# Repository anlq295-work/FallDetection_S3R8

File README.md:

# FallDetection_S3R8 (Fall Guard S3R8)

Hệ thống giám sát và phát hiện té ngã không tiếp xúc (non-contact, bảo vệ quyền riêng tư không dùng camera) chạy trên **ESP32-S3 N16R8** (16MB Flash, 8MB Octal PSRAM), kết hợp cảm biến đa phương thức (**ToF VL53L1X + 24GHz FMCW Radar HLK-LD2410B + PIR AM312**), bộ suy luận **Edge AI lai đa tiêu chí** và ứng dụng di động đa nền tảng **Flutter (Android & iOS)**.

> **Phiên bản hiện tại:** Firmware `Pre-release2.0.1` · Mobile App **Hearth** `Pre-release2.0.1` (`2.0.1+1`) · Target MCU: `esp32-s3-devkitc-1` (`qio_opi`)

---

## Mục lục

- [Tổng quan kiến trúc](#tổng-quan-kiến-trúc)
- [Tính năng nổi bật](#tính-năng-nổi-bật)
- [Cấu trúc thư mục](#cấu-trúc-thư-mục)
- [Phần cứng & Sơ đồ nối chân](#phần-cứng--sơ-đồ-nối-chân)
- [Thuật toán Edge AI & Máy trạng thái (FSM)](#thuật-toán-edge-ai--máy-trạng-thái-fsm)
- [Hướng dẫn Build & Cài đặt](#hướng-dẫn-build--cài-đặt)
- [Giao tiếp BLE, REST API & Lệnh điều khiển](#giao-tiếp-ble-rest-api--lệnh-điều-khiển)
- [Cập nhật Firmware OTA](#cập-nhật-firmware-ota)
- [CI/CD & Tự động phát hành](#cicd--tự-động-phát-hành)
- [Xử lý sự cố thường gặp](#xử-lý-sự-cố-thường-gặp)

---

## Tổng quan kiến trúc

```mermaid
flowchart LR
    subgraph SENSORS["Cụm cảm biến (20 Hz)"]
        TOF["VL53L1X ToF<br/>(I2C GPIO8/9)"]
        RADAR["HLK-LD2410B 24GHz Radar<br/>(UART2 GPIO17/18)"]
        PIR["PIR AM312<br/>(GPIO4 RTC IRQ)"]
        TOUCH["Touch SOS / Cancel<br/>(GPIO7)"]
    end

    subgraph MCU["ESP32-S3 N16R8 (16MB Flash / 8MB PSRAM)"]
        BUF["Circular Buffer (40 mẫu / 2s)<br/>Octal PSRAM"]
        AI["Edge AI Hybrid Engine<br/>(MLP 7→16→8→4 + Kinematic + Spatial)"]
        FSM["FSM 7 trạng thái<br/>+ WDT 10s + Hộp đen NVS"]
        LOCAL["WS2812B (24 LED) + Buzzer<br/>+ Smart Nightlight"]
        COMM["BLE GATT Server<br/>+ Wi-Fi Web Server (Port 80)<br/>+ OTA Manager"]
    end

    subgraph EXTERNAL["Giám sát & Cảnh báo từ xa"]
        APP["Flutter Mobile App<br/>(Android / iOS)"]
        TG["Telegram Bot API<br/>(HTML Alert)"]
        SMS["SpeedSMS Gateway"]
        GH["GitHub Releases<br/>(firmware.bin / APK / IPA)"]
    end

    TOF & RADAR & PIR --> BUF --> AI --> FSM
    TOUCH --> FSM
    FSM --> LOCAL
    FSM --> COMM
    COMM <-->|BLE / Wi-Fi LAN| APP
    COMM -->|HTTPS + Auto Retry| TG & SMS
    GH -->|HTTP / BLE / Web OTA| COMM
```

---

## Tính năng nổi bật

### 1. Firmware ESP32-S3 (`src/`)
- **Cảm biến đa phương thức & tự phục hồi lỗi:**
  - **VL53L1X (ToF):** Đo khoảng cách/chiều cao cơ thể qua I2C `100 kHz` (địa chỉ `0x29`, chế độ `Medium`, timing budget `40 ms`), tự giải phóng bus I2C bằng 9 xung clock nếu đường SDA bị treo `LOW` và tự khởi tạo lại khi mất dữ liệu.
  - **HLK-LD2410B (Radar mmWave 24GHz):** Tự động dò tốc độ baud (`256000` ↔ `115200`), bật **Engineering Mode** thu 9 cổng năng lượng chuyển động (va chạm) và 9 cổng năng lượng tĩnh (hô hấp/hiện diện).
  - **PIR AM312:** Phát hiện chuyển động hồng ngoại qua ngắt ngoài GPIO4 (có thể bật/tắt bằng macro `ENABLE_PIR_SENSOR`).
  - **Bộ đệm trượt Octal PSRAM:** Lấy mẫu `20 Hz` (chu kỳ `50 ms`), lưu cửa sổ trượt `40` mẫu (`2.0 s`) trực tiếp trên PSRAM ngoài (`MALLOC_CAP_SPIRAM`).
- **Phát hiện 3 kịch bản khẩn cấp:**
  1. **Té ngã va chạm mạnh (`EVENT_FALL_IMPACT`):** Kết hợp tốc độ sụt giảm chiều cao ToF, đỉnh động năng Radar và khoảng cách sát sàn, sau đó xác minh bất động `2 s` kèm tín hiệu tĩnh hô hấp.
  2. **Ngã chậm / Ngất lịm (`EVENT_SLOW_FALL`):** Nằm sát sàn (`<= floorThresholdMm`), ít chuyển động nhưng còn tín hiệu hiện diện/hô hấp kéo dài quá `15 s`.
  3. **SOS thủ công (`EVENT_MANUAL_SOS`):** Chạm giữ cảm biến touch (GPIO7) trong `3 s` hoặc kích hoạt lệnh `PANIC_SOS` từ xa.
- **Giảm báo động giả & tự giải trừ:**
  - Lọc phân biệt hành động ngồi xuống ghế (*SIT Rejection*).
  - Cảnh báo tại chỗ tầng 1 (`PRE_ALARM`) kéo dài `30 s` cho phép người dùng chạm nút hủy hoặc **tự đứng dậy vững vàng trong `1.5 s`** để hệ thống tự hủy cảnh báo.
- **Hoạt động độc lập khi không có điện thoại ở gần:**
  - Tự gửi cảnh báo trực tiếp qua **Telegram Bot API** (hỗ trợ nhiều Chat ID/Group ID phân tách bằng `,` hoặc `;`) và **SMS Gateway (SpeedSMS)** (hỗ trợ nhiều số điện thoại).
  - Nếu Wi-Fi bị gián đoạn đúng lúc có sự cố, firmware tự giữ hàng đợi và gửi lại định kỳ (`10 s` khi chờ Wi-Fi, `30 s` khi lỗi HTTP) cho tới khi thành công.
- **Tiện ích bổ trợ & An toàn hệ thống:**
  - **Đèn ngủ thông minh (Smart Nightlight):** Tự bật ánh sáng vàng ấm `40 s` trên dải LED WS2812B khi phát hiện di chuyển trong khung giờ hẹn lịch (mặc định `18:00 – 06:00`, đồng bộ giờ qua NTP `UTC+7`).
  - **Còi báo động chống tự kêu lúc boot:** Ngắt phần cứng ngay microgiây đầu tiên (`earlyHardwareMute()`), hỗ trợ đổi phân cực **Active-LOW / Active-HIGH** và **Mute/Unmute** lưu bền vững trong NVS Flash.
  - **Hộp đen NVS Flash:** Lưu vòng tròn 5 sự kiện té ngã gần nhất (loại sự kiện, uptime, tốc độ rơi, đỉnh động năng, cự ly radar).
  - **Hardware Watchdog Timer (`10 s`):** Tự reset nếu hệ thống treo.

### 2. Ứng dụng di động Flutter (`mobile_app/`)
- **Đa nền tảng Android & iOS**, giao diện Material 3 hỗ trợ chế độ Sáng/Tối theo hệ thống.
- **Kết nối kép BLE & Wi-Fi Direct LAN:** Quét thiết bị `FallDetector_S3R8`, cấu hình Wi-Fi, danh bạ cứu hộ (SĐT, Telegram Bot Token, Chat ID), ngưỡng sàn `floor_mm`, lịch đèn ngủ và phân cực/tắt tiếng còi.
- **Giám sát thời gian thực:** Hiển thị trạng thái FSM, phân loại tư thế AI + độ tin cậy, biểu đồ telemetry (`LiveTelemetryChart`), mô phỏng tư thế người (`HumanPostureSimulation`), và Hộp đen lịch sử sự cố.
- **Bộ công cụ chăm sóc & y tế cho người cao tuổi:**
  - Hướng dẫn sơ cứu trực quan từng bước (`FirstAidGuideDialog`).
  - Hồ sơ y tế khẩn cấp & Thẻ Medical ID (`ElderlyMedicalProfile`, `EmergencyMedicalIdCardDialog`).
  - Đánh giá nguy cơ té ngã theo chuẩn **CDC STEADI** (`CdcSteadiAssessmentDialog`).
  - Xuất/xem Báo cáo kiểm tra y tế (`MedicalAuditReportDialog`) & hộp thoại báo động khẩn cấp toàn màn hình (`CriticalEmergencyAlarmDialog`).
- **Cập nhật In-App OTA:** Tự kiểm tra bản phát hành mới nhất từ GitHub Releases cho cả ứng dụng lẫn firmware ESP32.

---

## Cấu trúc thư mục

```text
FallDetection_S3R8/
├── platformio.ini                 # Cấu hình PlatformIO cho ESP32-S3 N16R8 (16MB Flash, OPI PSRAM)
├── HARDWARE_PINOUT.md             # Chi tiết sơ đồ đấu nối & lưu ý cấp nguồn 5V
├── src/
│   ├── config.h                   # Pinout, ngưỡng động học, hằng số thời gian, enum FSM/AI
│   ├── main.cpp                   # Setup/Loop, FSM 7 trạng thái, xử lý lệnh BLE/HTTP/Serial & retry SOS
│   ├── sensors.h / sensors.cpp    # Driver VL53L1X, parser LD2410B auto-baud, PIR ISR, circular buffer PSRAM
│   ├── edge_ai.h / edge_ai.cpp    # Mạng MLP (7-16-8-4) + chấm điểm động học/không gian (Hybrid Fusion)
│   ├── model_data.h               # Dữ liệu tham chiếu mô hình INT8 (TFLM)
│   ├── alert_system.h / .cpp      # Điều khiển WS2812B, Buzzer patterns, Nightlight, Wi-Fi, Telegram & SMS
│   ├── ble_provision.h / .cpp     # BLE GATT Server (6 characteristics), NVS config & Hộp đen 5 sự kiện
│   ├── web_server.h / .cpp        # HTTP Server cổng 80 (REST API + trang Web OTA /update)
│   └── ota_manager.h / .cpp       # Quản lý HTTP/HTTPS OTA và BLE OTA chunk stream
├── alert_bot/                     # Bot cảnh báo đa kênh (Telegram tương tác + SMS + CallMeBot/Twilio Voice)
│   ├── server.py                  # FastAPI REST API + Webhook nhận sự kiện ngã (/api/alerts/fall)
│   ├── dispatcher.py              # Phát cảnh báo đồng thời / leo thang tuần tự + xác nhận/đóng sự cố
│   ├── telegram_poller.py         # Telegram Bot (/start, /register, /settings, /contacts, /test, nút bấm)
│   ├── providers/                 # Telegram Bot API, SpeedSMS VN, Twilio SMS/Voice, CallMeBot Telegram Call
│   └── tests/                     # Unit & integration tests (pytest)
├── mobile_app/                    # Ứng dụng Flutter (Android & iOS)
│   ├── pubspec.yaml               # Dependencies: flutter_blue_plus, url_launcher, shared_preferences, ...
│   ├── README.md                  # Tài liệu riêng cho ứng dụng di động
│   └── lib/
│       ├── main.dart              # Entrypoint, Theme Material 3 & khai báo BLE UUID
│       ├── startup.dart           # Cổng xin quyền Bluetooth/Nearby Devices khi khởi động
│       ├── dashboard.dart         # Màn hình quét, kết nối & tổng quan thiết bị
│       ├── device_detail.dart     # Bảng điều khiển chi tiết, cấu hình thiết bị, OTA & Hộp đen
│       ├── telemetry_widgets.dart # Biểu đồ telemetry & mô phỏng tư thế người
│       ├── settings.dart          # Cài đặt chung, đơn vị đo & kiểm tra cập nhật GitHub Release
│       └── dialogs.dart           # Sơ cứu, Hồ sơ y tế, CDC STEADI, báo cáo y tế & cảnh báo SOS
├── ios_ota/
│   └── manifest.plist             # Manifest cài đặt OTA cho iOS
├── scripts/
│   └── pull_artifacts.py          # Script Python tải tự động APK/IPA/Firmware từ GitHub Actions
└── .github/workflows/
    └── build_apps.yml             # CI/CD build Android APK, iOS IPA, ESP32 firmware & publish Release
```

---

## Phần cứng & Sơ đồ nối chân

### Danh sách linh kiện chính
- **Vi điều khiển:** ESP32-S3 N16R8 DevKitC-1 (16MB QIO Flash, 8MB Octal OPI PSRAM).
- **Cảm biến khoảng cách:** ToF Laser **VL53L1X** (I2C, 3.3V).
- **Radar sóng milimet:** **HLK-LD2410B** 24GHz FMCW (UART, 5V).
- **Cảm biến hồng ngoại:** **PIR AM312** (3.3V).
- **Nút cảm ứng:** Module Touch (Active-HIGH, 3.3V).
- **Đầu ra báo động:** Thanh/vòng LED **WS2812B** (24 LED, 5V) + **Active Buzzer 5V** (kèm mạch driver transistor/MOSFET).

### Bảng nối chân (Pinout)

> **Cảnh báo:** Tuyệt đối không sử dụng **GPIO33 – GPIO37** trên ESP32-S3 N16R8 vì dành riêng cho Octal PSRAM/OPI Flash, và không nối nút cảm ứng vào **GPIO0** (chân BOOT).

| Module / Thiết bị | Chân ESP32-S3 | Giao tiếp / Ghi chú |
| :--- | :---: | :--- |
| **PIR AM312 OUT** | `GPIO4` | Ngắt ngoài RTC (`RISING`), nguồn 3.3V |
| **Buzzer Module IN** | `GPIO5` | Mặc định Active-LOW (đổi được qua BLE/Serial); dùng mạch driver, không kéo tải trực tiếp |
| **WS2812B DIN** | `GPIO6` | 24 LED RGB, độ sáng mặc định `100/255`, cấp nguồn 5V riêng, chung GND |
| **Touch Module OUT** | `GPIO7` | Active-HIGH (`INPUT_PULLDOWN`): chạm ngắn hủy báo động, chạm giữ `3 s` kích SOS |
| **VL53L1X SDA** | `GPIO8` | I2C `100 kHz`, địa chỉ `0x29`, logic 3.3V |
| **VL53L1X SCL** | `GPIO9` | I2C `100 kHz`, logic 3.3V |
| **LD2410B RX** | `GPIO17` | `Serial2 TX` (ESP32 TX → Radar RX) |
| **LD2410B TX** | `GPIO18` | `Serial2 RX` (Radar TX → ESP32 RX, `INPUT_PULLUP`) |

### Lưu ý cấp nguồn
- Dùng nguồn **5V ổn định tối thiểu 2A** (khuyến nghị **3A** khi bật toàn bộ 24 LED WS2812B), đấu vào chân `5V/VBUS` (không cấp nguồn ngoài vào chân `3V3`).
- Nối chung **GND** cho ESP32-S3 và toàn bộ cảm biến/LED; nên đặt tụ lọc `470–1000 µF` gần dải LED WS2812B để tránh sụt áp gây mất BLE khi khởi động.
- Xem chi tiết thêm tại [HARDWARE_PINOUT.md](HARDWARE_PINOUT.md).

---

## Thuật toán Edge AI & Máy trạng thái (FSM)

### 7 đặc trưng đầu vào (cửa sổ trượt 2.0 giây)
1. `f[0]` – `maxMotion`: Đỉnh năng lượng chuyển động Radar LD2410 (`0–100`).
2. `f[1]` – `maxStatic`: Đỉnh năng lượng tĩnh / hô hấp Radar LD2410 (`0–100`).
3. `f[2..4]` – `tofHigh`, `tofMid`, `tofLow`: Cự ly đo ToF mới nhất (`mm`).
4. `f[5]` – `dropRate`: Tốc độ sụt giảm chiều cao trung bình giữa 5 mẫu đầu và 5 mẫu cuối cửa sổ (`mm/s`).
5. `f[6]` – `radarDist`: Khoảng cách tới mục tiêu từ Radar (`cm`).

### Công thức kết hợp lai (Hybrid Fusion)
$$\text{finalFallConf} = 0.25 \times P_{\text{MLP}}(\text{FALL}) + 0.45 \times S_{\text{kinematic}} + 0.30 \times S_{\text{spatial}}$$

- **Ngưỡng chính trong `src/config.h`:**
  - `FALL_VELOCITY_THRESH_MM_S = 550 mm/s` (`STRONG = 700 mm/s`)
  - `FALL_RADAR_MOTION_THRESH = 40/100` (`STRONG = 70/100`)
  - `FLOOR_HEIGHT_DEFAULT_MM = 450 mm` · `SIT_HEIGHT_MIN_MM = 480 mm` · `STAND_HEIGHT_MIN_MM = 900 mm`
- Chỉ xác nhận `CLASS_FALL` khi `finalFallConf >= 0.62` **và** thỏa tối thiểu 2 dấu hiệu đồng thời: `(velTrig && impTrig)` hoặc `(strongVelocity && floorTrig)` hoặc `(strongImpact && floorTrig)`.

### Luồng chuyển trạng thái FSM

```mermaid
stateDiagram-v2
    [*] --> NORMAL
    NORMAL --> SUSPECTED: AI phát hiện FALL
    NORMAL --> PRE_ALARM: Nằm sàn bất động >= 15s (Slow Fall)
    NORMAL --> ALERT: Chạm giữ Touch 3s / Lệnh PANIC_SOS

    SUSPECTED --> PRE_ALARM: Sau 2s xác nhận sát sàn + bất động (<=25) + còn tĩnh (>=15)
    SUSPECTED --> NORMAL: Người di chuyển tiếp (bỏ qua báo giả)

    PRE_ALARM --> RESOLVED: Tự đứng dậy >= 1.5s hoặc hủy thủ công
    PRE_ALARM --> ALERT: Hết 30s không phản hồi

    ALERT --> ACKNOWLEDGED: Ghi Hộp đen NVS + Xếp hàng gửi Telegram/SMS
    ACKNOWLEDGED --> RESOLVED: Chạm Touch hoặc lệnh CANCEL_ALARM
    RESOLVED --> NORMAL: Sau 1s xác nhận

    NORMAL --> DEVICE_FAULT: Lỗi khởi tạo cảm biến / AI
    DEVICE_FAULT --> NORMAL: Tự khởi tạo lại cảm biến thành công (mỗi 5s)
```

### Quy ước màu đèn LED trạng thái
| Trạng thái | LED WS2812B | Còi Buzzer |
| :--- | :--- | :--- |
| Khởi động (`setup`) | Tím Magenta | Tắt (mặc định `ENABLE_STARTUP_BEEP = 0`) |
| `STATE_NORMAL` | Xanh lá (`#00FF00`) / Vàng ấm khi bật Nightlight | Im lặng |
| `STATE_SUSPECTED` | Vàng tối (`#332200`) | Im lặng |
| `STATE_PRE_ALARM` | Nhấp nháy Cam (`#FFA500`, chu kỳ 250ms) | Bíp đôi định kỳ (`BUZZER_PRE_ALARM_PULSE`) |
| `STATE_ALERT` | Đỏ (`#FF0000`) | Còi hú dồn dập (`BUZZER_ALERT_SIREN`) |
| `STATE_ACKNOWLEDGED` | Nhấp nháy Đỏ (`#FF0000`, chu kỳ 500ms) | Tắt để tránh hoảng loạn |
| `STATE_DEVICE_FAULT` | Nhấp nháy Tím (`#9600FF`, chu kỳ 200ms) | Im lặng |
| Đang nạp OTA HTTP | Tím đậm (`#800080`) | Im lặng |

---

## Hướng dẫn Build & Cài đặt

### 1. Firmware ESP32-S3 (PlatformIO)

**Yêu cầu:** [PlatformIO Core (CLI)](https://platformio.org/) hoặc VS Code kèm extension PlatformIO IDE.

```bash
# Build firmware
pio run -e esp32-s3-n16r8

# Nạp firmware vào mạch ESP32-S3 N16R8
pio run -e esp32-s3-n16r8 --target upload

# Mở Serial Monitor (115200 baud)
pio device monitor -b 115200
```

> **Lưu ý cấu hình SMS Gateway:** Trước khi dùng tính năng gửi SMS qua SpeedSMS, cập nhật `DEFAULT_SMS_TOKEN` (và `DEFAULT_SMS_GATEWAY_URL` nếu đổi nhà cung cấp) trong `src/config.h`. Thông tin Wi-Fi, Telegram Bot Token, Chat ID và SĐT nhận tin có thể cấu hình trực tiếp từ Mobile App qua BLE mà không cần biên dịch lại.

**Phím tắt debug nhanh trên Serial Monitor (`115200 baud`):**
- `T` – Phát tiếng bíp test còi (`200 ms`)
- `H` – Chuyển còi sang chế độ `Active-HIGH` (lưu vào NVS)
- `L` – Chuyển còi sang chế độ `Active-LOW` (lưu vào NVS)
- `M` – Bật / tắt chế độ im lặng (`Mute`)
- `S` – In trạng thái FSM, pattern còi, phân cực và giá trị chân GPIO5

### 2. Mobile App (Flutter)

**Yêu cầu:** Flutter SDK (kèm Dart SDK `^3.11.5`), Android Studio (cho Android) hoặc macOS + Xcode (cho iOS).

```bash
cd mobile_app
flutter pub get

# Chạy trực tiếp trên thiết bị thật
flutter run

# Build Android Release APK
flutter build apk --release
# Output: mobile_app/build/app/outputs/flutter-apk/app-release.apk

# Build iOS (cần macOS + Xcode)
flutter build ipa
```

---

## Giao tiếp BLE, REST API & Lệnh điều khiển

### 1. BLE GATT Profile (`FallDetector_S3R8`, MTU 512)

- **Service UUID:** `4fafc201-1fb5-459e-8fcc-c5c9c331914b`

| Characteristic | UUID | Thuộc tính | Định dạng / Chức năng |
| :--- | :--- | :--- | :--- |
| **Wi-Fi Config** | `0beb5483-e18e-4f36-9e1b-b4d6b63c7b28` | `WRITE` | `{"ssid":"...","pass":"..."}` → Lưu NVS và tự reboot |
| **Contact & Floor** | `1c6f8742-9a6d-4785-b9e1-e63f9b8c0011` | `READ`, `WRITE` | `{"phone":"...","chat_id":"...","bot_token":"...","floor_mm":450}` |
| **Status** | `2d8a9e22-7f1c-4b53-8d2a-f58c7e9a3344` | `READ`, `NOTIFY` | Chuỗi trạng thái (`CONNECTED_IP:...`, `OTA_PROGRESS:50`, `REMOTE_ALERT_SENT`, ...) |
| **Telemetry** | `3e9baf33-8a2d-4c64-9e3b-a69d8f0b4455` | `READ`, `NOTIFY` | Notify mỗi `250 ms`: `{"st":"NORMAL","cls":"STAND","cf":0.92,"h":1200,"m":12,"s":20,"dr":0,"pir":0,"ip":"...","rssi":-55,"uptime":120,"ver":"v2.0.0"}` |
| **Command** | `4fa0b044-9b3e-4d75-af4c-b70e901c5566` | `WRITE` | Gửi lệnh điều khiển dạng văn bản thuần (xem bảng dưới) |
| **BLE OTA** | `5fa0b055-9b3e-4d75-af4c-b70e901c5566` | `WRITE`, `WRITE_NR` | `OTA_BEGIN:<bytes>`, binary chunks, `OTA_END`, `OTA_ABORT` |

### 2. Wi-Fi LAN HTTP REST API (Cổng 80)

Khi ESP32 kết nối Wi-Fi thành công, Web Server tự động chạy tại `http://<ESP32_IP>/` (hỗ trợ đầy đủ CORS):

| Method | Endpoint | Mô tả |
| :--- | :--- | :--- |
| `GET` | `/` | Trang giới thiệu các API có sẵn |
| `GET` | `/api/telemetry` (hoặc `/telemetry`) | JSON telemetry thời gian thực (cùng định dạng với BLE) |
| `GET` | `/api/events` (hoặc `/events`) | JSON lịch sử 5 sự kiện trong Hộp đen NVS Flash |
| `GET` | `/api/status` | JSON thông số phần cứng, trạng thái Wi-Fi, `free_heap`, `floor_mm`, cấu hình còi, trạng thái gửi SOS |
| `GET` / `POST` | `/api/command` | Thực thi lệnh qua query `?cmd=<CMD>` hoặc body JSON `{"cmd":"<CMD>"}` |
| `GET` / `POST` | `/api/config` | Đọc / đồng bộ danh bạ cứu hộ, Telegram, CallMeBot, URL Alert Bot & channel mask qua Wi-Fi LAN |
| `GET` / `POST` | `/update` | Trang Web OTA upload trực tiếp file `firmware.bin` |

### 3. Danh sách lệnh điều khiển (`CHAR_CMD_UUID` & `/api/command`)

| Lệnh | Tác dụng |
| :--- | :--- |
| `CALIBRATE_FLOOR` | Hiệu chuẩn ngưỡng sàn từ khoảng cách ToF hiện tại và lưu NVS |
| `CANCEL_ALARM` | Hủy cảnh báo/SOS, tắt còi, reset trạng thái về `NORMAL` |
| `PANIC_SOS` | Kích hoạt cảnh báo khẩn cấp SOS từ xa ngay lập tức |
| `TEST_ALARM` / `TEST_BEEP` | Kiểm tra còi + LED đỏ (`400 ms`) hoặc bíp ngắn (`200 ms`) |
| `TEST_REMOTE_ALERT` | Gửi thử cảnh báo ngã qua Alert Bot Server (hoặc fallback trực tiếp Telegram / SMS / CallMeBot) |
| `GET_HISTORY` / `CLEAR_HISTORY` / `ADD_TEST_EVENT` | Đọc, xóa hoặc thêm sự kiện giả lập vào Hộp đen NVS |
| `BUZZER_ACTIVE_LOW` / `BUZZER_ACTIVE_HIGH` | Đổi phân cực còi và lưu vĩnh viễn vào NVS |
| `BUZZER_MUTE` / `BUZZER_UNMUTE` | Tắt/mở tiếng còi hoàn toàn (phục vụ test lab yên tĩnh) |
| `NIGHTLIGHT_SCHEDULE:<en>,<sh>,<sm>,<eh>,<em>` | Cài lịch bật đèn ngủ (VD: `NIGHTLIGHT_SCHEDULE:1,18,0,6,0`) |
| `OTA_LATEST` / `OTA_HTTP:<url>` | Tải và nạp firmware trực tiếp qua Wi-Fi HTTPS/HTTP |
| `GET_VERSION` | Trả về phiên bản firmware hiện tại qua Status Notify |
| `REBOOT` | Khởi động lại ESP32-S3 |
| `RESET_NETWORK` | Xóa SSID/Password Wi-Fi đã lưu và khởi động lại |
| `FACTORY_RESET` | Xóa toàn bộ NVS Flash về mặc định xuất xưởng và khởi động lại |

---

## Cập nhật Firmware OTA

Thiết bị hỗ trợ **3 phương thức nâng cấp Firmware không dây**:

1. **HTTPS OTA qua GitHub Releases (Khuyên dùng):**
   - Gửi lệnh `OTA_LATEST` (hoặc `OTA_HTTP:<custom_url>`) qua BLE hoặc `/api/command`.
   - ESP32 tự tải `firmware.bin` từ release `latest` trên GitHub, gửi tiến độ `OTA_PROGRESS:<0..100>` về App và tự khởi động lại.
2. **Web OTA trong mạng LAN:**
   - Mở trình duyệt tới `http://<ESP32_IP>/update`, chọn file `.pio/build/esp32-s3-n16r8/firmware.bin` và bấm nạp.
3. **BLE OTA (Không cần Wi-Fi):**
   - App gửi `OTA_BEGIN:<fileSize>` vào `CHAR_OTA_UUID`, truyền liên tiếp các chunk nhị phân, sau đó gửi `OTA_END` để xác thực và reboot.

---

## CI/CD & Tự động phát hành

Workflow `.github/workflows/build_apps.yml` tự động chạy khi push lên `main`/`master`, gắn tag `v*`, mở PR hoặc kích hoạt thủ công (`workflow_dispatch`):

1. **`prepare-version`:** Tự động tính Semantic Version và lọc phát hành thông minh:
   - **Không tăng version (cập nhật lại asset trong Release hiện tại)** khi chỉ sửa tài liệu/CI/test/cấu hình (`README.md`, `CHANGELOG.md`, `.github/workflows/*`, `scripts/*`, `analysis_options.yaml`, `mobile_app/test/*`) hoặc khi commit bắt đầu bằng `ci:`, `docs:`, `chore:`, `test:`, `style:`, `build:`, `refactor:` hoặc chứa `[no-release]` / `[skip release]`. Các tệp APK/IPA/firmware mới dựng vẫn tự động thay thế tệp cũ trong Release hiện tại (không tạo trùng lặp).
   - **Tự động tăng version & tạo Release mới** khi có thay đổi mã app/firmware (`src/`, `mobile_app/lib/`, `platformio.ini`, ...) theo mức `[major]` / `breaking change`, `[minor]` / `feat:`, mặc định `patch`, hoặc khi có từ khóa `[release]`, push tag `v*`, hay chạy thủ công `workflow_dispatch`.
2. **`build-android`:** Chạy `flutter analyze --no-fatal-infos`, `flutter test` và build Release APK (`Hearth-Android-v<ver>-build-<num>.apk`).
3. **`build-ios`:** Chạy trên `macos-latest`, đóng gói bản `-unsigned.ipa` (và tự động ký số `-signed.ipa` vào Artifacts riêng nếu đã khai báo secrets `APPLE_CERT_P12_BASE64`, `APPLE_CERT_PASSWORD`, `APPLE_PROVISION_PROFILE_BASE64`).
4. **`build-firmware`:** Chạy `pio run -e esp32-s3-n16r8` tạo `firmware.bin`.
5. **`publish-release`:** Chỉ chạy khi `should_release == 'true'`; tự động sinh Release Notes chi tiết từ `CHANGELOG.md` + git commits kèm bảng SHA-256 và phát hành 1 Release chính thức duy nhất (`v<ver>`, `make_latest: true`).

### Tải nhanh Artifacts từ GitHub Actions về máy
```bash
# Tải artifacts từ lần build thành công gần nhất
python scripts/pull_artifacts.py

# Hoặc chờ workflow đang chạy hoàn tất rồi tự động tải về
python scripts/pull_artifacts.py --wait
```

---

## Xử lý sự cố thường gặp

- **Cắm USB chạy bình thường nhưng cấp nguồn ngoài 5V mất BLE:** Thường do sụt áp đường `3V3` (< `3.1V`) khi 24 LED WS2812B khởi động, thiếu GND chung hoặc chân `GPIO0` bị kéo `LOW`. Đo lại nguồn 5V/3V3 khi khởi động, dùng nguồn 5V 2A–3A và gắn tụ `470–1000 µF` gần LED.
- **Không thấy Octal PSRAM trên Serial Monitor:** Kiểm tra cấu hình `board_build.arduino.memory_type = qio_opi` và `-DBOARD_HAS_PSRAM` trong `platformio.ini`.
- **Còi tự kêu liên tục khi mới cấp nguồn:** Kiểm tra phân cực module còi; gửi lệnh `BUZZER_ACTIVE_HIGH` hoặc `BUZZER_ACTIVE_LOW` (qua App hoặc nhấn `H`/`L` trên Serial Monitor) để khớp với phần cứng.
- **ToF VL53L1X báo lỗi `STATE_DEVICE_FAULT`:** Kiểm tra dây `SDA (GPIO8)` / `SCL (GPIO9)` và nguồn `3.3V`; firmware sẽ tự thử khôi phục I2C và khởi tạo lại mỗi `5 giây`.

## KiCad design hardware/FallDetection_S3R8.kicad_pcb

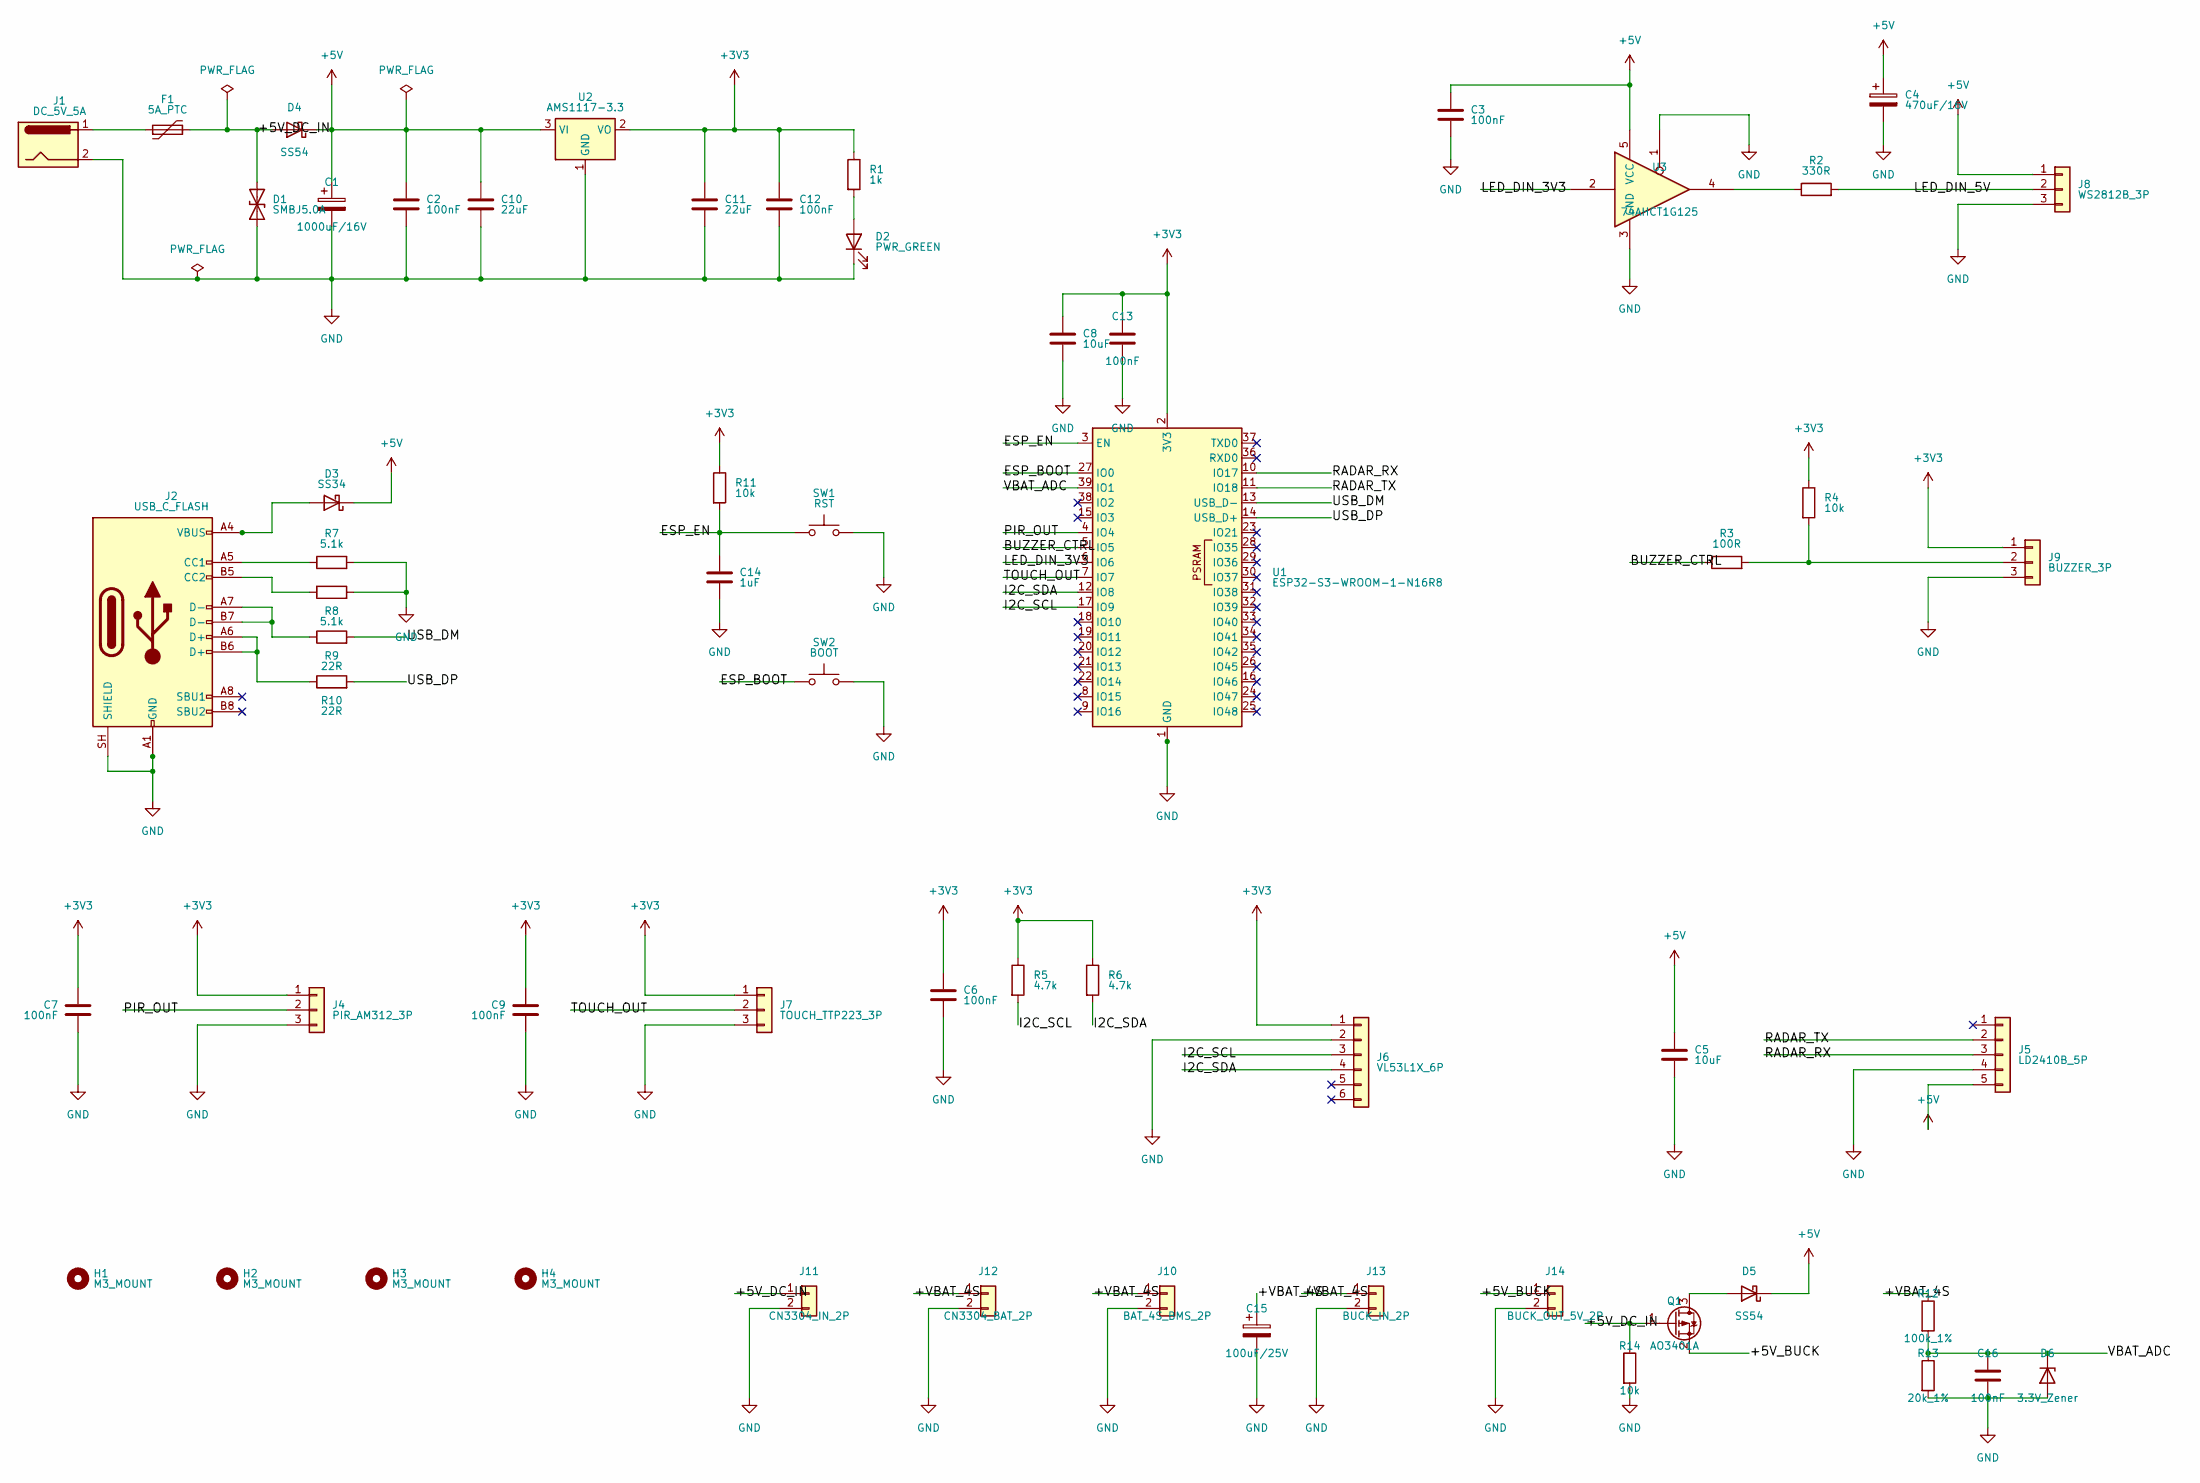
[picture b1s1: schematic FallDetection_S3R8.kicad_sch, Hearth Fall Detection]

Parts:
C1: 1000uF/16V; CP_Radial_D10.0mm_P5.00mm
C2, C3, C6, C7, C9, C12, C13, C16: 100nF; C_0805_2012Metric
C4: 470uF/16V; CP_Radial_D10.0mm_P5.00mm
C5, C8: 10uF; C_0805_2012Metric
C10, C11: 22uF; C_0805_2012Metric
C14: 1uF; C_0805_2012Metric
C15: 100uF/25V; CP_Radial_D8.0mm_P3.50mm
D1: SMBJ5.0A; D_SMB
D2: PWR_GREEN; LED_0805_2012Metric
D3: SS34; D_SMA
D4, D5: SS54; D_SMB
D6: 3.3V_Zener; D_SOD-123
F1: 5A_PTC; Fuse_1812_4532Metric
H1, H2, H3, H4: M3_MOUNT; MountingHole_3.2mm_M3
J1: DC_5V_5A; BarrelJack_CUI_PJ-102AH_Horizontal
J2: USB_C_FLASH; USB_C_Receptacle_GCT_USB4105-xx-A_16P_TopMnt_Horizontal
J4: PIR_AM312_3P; PinHeader_1x03_P2.54mm_Vertical
J5: LD2410B_5P; PinHeader_1x05_P2.54mm_Vertical
J6: VL53L1X_6P; PinHeader_1x06_P2.54mm_Vertical
J7: TOUCH_TTP223_3P; PinHeader_1x03_P2.54mm_Vertical
J8: WS2812B_3P; PinHeader_1x03_P2.54mm_Vertical
J9: BUZZER_3P; PinHeader_1x03_P2.54mm_Vertical
J10: BAT_4S_BMS_2P; TerminalBlock_Phoenix_MKDS-1,5-2-5.08_1x02_P5.08mm_Horizont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
J11: CN3304_IN_2P; PinHeader_1x02_P2.54mm_Vertical
J12: CN3304_BAT_2P; PinHeader_1x02_P2.54mm_Vertical
J13: BUCK_IN_2P; PinHeader_1x02_P2.54mm_Vertical
J14: BUCK_OUT_5V_2P; PinHeader_1x02_P2.54mm_Vertical
Q1: AO3401A; SOT-23
R1: 1k; R_0805_2012Metric
R2: 330R; R_0805_2012Metric
R3: 100R; R_0805_2012Metric
R4, R11, R14: 10k; R_0805_2012Metric
R5, R6: 4.7k; R_0805_2012Metric
R7, R8: 5.1k; R_0805_2012Metric
R9, R10: 22R; R_0805_2012Metric
R12: 100k_1%; R_0805_2012Metric
R13: 20k_1%; R_0805_2012Metric
SW1: RST; SW_SPST_TL3342
SW2: BOOT; SW_SPST_TL3342
U1: ESP32-S3-WROOM-1-N16R8; ESP32-S3-WROOM-1
U2: AMS1117-3.3; SOT-223-3_TabPin2
U3: 74AHCT1G125; SOT-23-5

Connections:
+3V3: C6.1, C7.1, C8.1, C9.1, C11.1, C12.1, C13.1, J4.1, J6.1, J7.1, J9.1, R1.1, R4.1, R5.1, R6.1, R11.1, U1.2 (3V3), U2.2 (VO)
+5V: C1.1, C2.1, C3.1, C4.1, C5.1, C10.1, D3.1 (K), D4.1 (K), D5.1 (K), J5.5, J8.1, U2.3 (VI), U3.5 (VCC)
/+5V_BUCK: J14.1, Q1.2 (S)
/+5V_DC_IN: D1.2 (A2), D4.2 (A), F1.2, J11.1, Q1.1 (G), R14.1
/+VBAT_4S: C15.1, J10.1, J12.1, J13.1, R12.1
/BUZZER_CTRL: R3.1, U1.5 (IO5)
/ESP_BOOT: SW2.1, U1.27 (IO0)
/ESP_EN: C14.1, R11.2, SW1.1, U1.3 (EN)
/I2C_SCL: J6.3, R5.2, U1.17 (IO9)
/I2C_SDA: J6.4, R6.2, U1.12 (IO8)
/LED_DIN_3V3: U1.6 (IO6), U3.2
/LED_DIN_5V: J8.2, R2.2
/PIR_OUT: J4.2, U1.4 (IO4)
/RADAR_RX: J5.3, U1.10 (IO17)
/RADAR_TX: J5.2, U1.11 (IO18)
/TOUCH_OUT: J7.2, U1.7 (IO7)
/USB_DM: R9.2, U1.13 (USB_D-)
/USB_DP: R10.2, U1.14 (USB_D+)
/VBAT_ADC: C16.1, D6.1 (K), R12.2, R13.1, U1.39 (IO1)
GND: C1.2, C2.2, C3.2, C4.2, C5.2, C6.2, C7.2, C8.2, C9.2, C10.2, C11.2, C12.2, C13.2, C14.2, C15.2, C16.2, D1.1 (A1), D2.1 (K), D6.2 (A), J1.2, J2.A1 (GND), J2.A12 (GND), J2.B1 (GND), J2.B12 (GND), J2.SH (SHIELD), J4.3, J5.4, J6.2, J7.3, J8.3, J9.3, J10.2, J11.2, J12.2, J13.2, J14.2, R7.2, R8.2, R13.2, R14.2, SW1.2, SW2.2, U1.1 (GND), U1.40 (GND), U1.41 (GND), U2.1 (GND), U3.1, U3.3 (GND)
unnamed: D2.2 (A), R1.2
unnamed: D3.2 (A), J2.A4 (VBUS), J2.A9 (VBUS), J2.B4 (VBUS), J2.B9 (VBUS)
unnamed: D5.2 (A), Q1.3 (D)
unnamed: F1.1, J1.1
unnamed: J2.A5 (CC1), R7.1
unnamed: J2.B5 (CC2), R8.1
unnamed: J2.A6 (D+), J2.B6 (D+), R10.1
unnamed: J2.A7 (D-), J2.B7 (D-), R9.1
unnamed: J9.2, R3.2, R4.2
unnamed: R2.1, U3.4

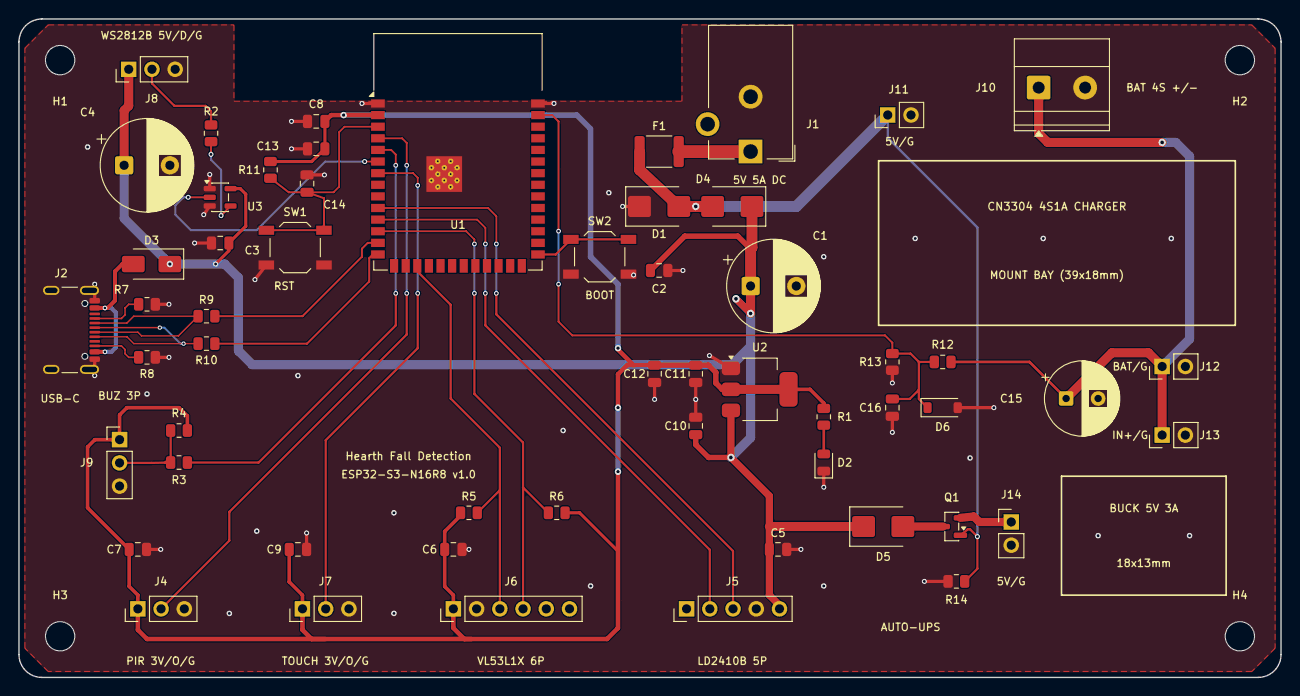
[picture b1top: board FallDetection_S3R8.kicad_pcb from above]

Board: 2 copper layers, 138.0 x 72.0 mm, 60 parts (0 on the bottom side), 30 nets.

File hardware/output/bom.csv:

"Refs","Value","Footprint","Qty","DNP"
"C1","1000uF/16V","Capacitor_THT:CP_Radial_D10.0mm_P5.00mm","1",""
"C2","100nF","Capacitor_SMD:C_0805_2012Metric","1",""
"C3","100nF","Capacitor_SMD:C_0805_2012Metric","1",""
"C4","470uF/16V","Capacitor_THT:CP_Radial_D10.0mm_P5.00mm","1",""
"C5","10uF","Capacitor_SMD:C_0805_2012Metric","1",""
"C6","100nF","Capacitor_SMD:C_0805_2012Metric","1",""
"C7","100nF","Capacitor_SMD:C_0805_2012Metric","1",""
"C8","10uF","Capacitor_SMD:C_0805_2012Metric","1",""
"C9","100nF","Capacitor_SMD:C_0805_2012Metric","1",""
"C10","22uF","Capacitor_SMD:C_0805_2012Metric","1",""
"C11","22uF","Capacitor_SMD:C_0805_2012Metric","1",""
"C12","100nF","Capacitor_SMD:C_0805_2012Metric","1",""
"C13","100nF","Capacitor_SMD:C_0805_2012Metric","1",""
"C14","1uF","Capacitor_SMD:C_0805_2012Metric","1",""
"C15","100uF/25V","Capacitor_THT:CP_Radial_D8.0mm_P3.50mm","1",""
"C16","100nF","Capacitor_SMD:C_0805_2012Metric","1",""
"D1","SMBJ5.0A","Diode_SMD:D_SMB","1",""
"D2","PWR_GREEN","LED_SMD:LED_0805_2012Metric","1",""
"D3","SS34","Diode_SMD:D_SMA","1",""
"D4","SS54","Diode_SMD:D_SMB","1",""
"D5","SS54","Diode_SMD:D_SMB","1",""
"D6","3.3V_Zener","Diode_SMD:D_SOD-123","1",""
"F1","5A_PTC","Fuse:Fuse_1812_4532Metric","1",""
"H1","M3_MOUNT","MountingHole:MountingHole_3.2mm_M3","1",""
"H2","M3_MOUNT","MountingHole:MountingHole_3.2mm_M3","1",""
"H3","M3_MOUNT","MountingHole:MountingHole_3.2mm_M3","1",""
"H4","M3_MOUNT","MountingHole:MountingHole_3.2mm_M3","1",""
"J1","DC_5V_5A","Connector_BarrelJack:BarrelJack_CUI_PJ-102AH_Horizontal","1",""
"J2","USB_C_FLASH","Connector_USB:USB_C_Receptacle_GCT_USB4105-xx-A_16P_TopMnt_Horizontal","1",""
"J4","PIR_AM312_3P","Connector_PinHeader_2.54mm:PinHeader_1x03_P2.54mm_Vertical","1",""
"J5","LD2410B_5P","Connector_PinHeader_2.54mm:PinHeader_1x05_P2.54mm_Vertical","1",""
"J6","VL53L1X_6P","Connector_PinHeader_2.54mm:PinHeader_1x06_P2.54mm_Vertical","1",""
"J7","TOUCH_TTP223_3P","Connector_PinHeader_2.54mm:PinHeader_1x03_P2.54mm_Vertical","1",""
"J8","WS2812B_3P","Connector_PinHeader_2.54mm:PinHeader_1x03_P2.54mm_Vertical","1",""
"J9","BUZZER_3P","Connector_PinHeader_2.54mm:PinHeader_1x03_P2.54mm_Vertical","1",""
"J10","BAT_4S_BMS_2P","TerminalBlock_Phoenix:TerminalBlock_Phoenix_MKDS-1,5-2-5.08_1x02_P5.08mm_Horizontal","1",""
"J11","CN3304_IN_2P","Connector_PinHeader_2.54mm:PinHeader_1x02_P2.54mm_Vertical","1",""
"J12","CN3304_BAT_2P","Connector_PinHeader_2.54mm:PinHeader_1x02_P2.54mm_Vertical","1",""
"J13","BUCK_IN_2P","Connector_PinHeader_2.54mm:PinHeader_1x02_P2.54mm_Vertical","1",""
"J14","BUCK_OUT_5V_2P","Connector_PinHeader_2.54mm:PinHeader_1x02_P2.54mm_Vertical","1",""
"Q1","AO3401A","Package_TO_SOT_SMD:SOT-23","1",""
"R1","1k","Resistor_SMD:R_0805_2012Metric","1",""
"R2","330R","Resistor_SMD:R_0805_2012Metric","1",""
"R3","100R","Resistor_SMD:R_0805_2012Metric","1",""
"R4","10k","Resistor_SMD:R_0805_2012Metric","1",""
"R5","4.7k","Resistor_SMD:R_0805_2012Metric","1",""
"R6","4.7k","Resistor_SMD:R_0805_2012Metric","1",""
"R7","5.1k","Resistor_SMD:R_0805_2012Metric","1",""
"R8","5.1k","Resistor_SMD:R_0805_2012Metric","1",""
"R9","22R","Resistor_SMD:R_0805_2012Metric","1",""
"R10","22R","Resistor_SMD:R_0805_2012Metric","1",""
"R11","10k","Resistor_SMD:R_0805_2012Metric","1",""
"R12","100k_1%","Resistor_SMD:R_0805_2012Metric","1",""
"R13","20k_1%","Resistor_SMD:R_0805_2012Metric","1",""
"R14","10k","Resistor_SMD:R_0805_2012Metric","1",""
"SW1","RST","Button_Switch_SMD:SW_SPST_TL3342","1",""
"SW2","BOOT","Button_Switch_SMD:SW_SPST_TL3342","1",""
"U1","ESP32-S3-WROOM-1-N16R8","RF_Module:ESP32-S3-WROOM-1","1",""
"U2","AMS1117-3.3","Package_TO_SOT_SMD:SOT-223-3_TabPin2","1",""
"U3","74AHCT1G125","Package_TO_SOT_SMD:SOT-23-5","1",""

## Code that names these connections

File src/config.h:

#ifndef CONFIG_H
#define CONFIG_H

#include <Arduino.h>

// Phiên bản Firmware hệ thống
#define FIRMWARE_VERSION            "pre-release1.4.0"

// =========================================================================
// 1. PINOUT AN TOÀN CHO ESP32-S3R8 & CẤU HÌNH CẢM BIẾN
// (LƯU Ý CỰC KỲ QUAN TRỌNG: TRÁNH TUYỆT ĐỐI CÁC CHÂN TỪ GPIO 33 ĐẾN 37 VÌ DÀNH CHO OCTAL PSRAM/OPI FLASH)
// =========================================================================
#define ENABLE_PIR_SENSOR     1     // Đặt 1: Bật cảm biến hồng ngoại PIR AM312 (chân GPIO 4 ngắt ngoài RTC)
#define PIN_PIR               4     // PIR AM312 (Ngắt ngoài RTC)
#define PIN_BUZZER            5     // Active Buzzer 5V

// Cấu hình phân cực Còi Báo Động (Active Buzzer Module Polarity):
// • Đặt 0: Mặc định chuẩn module còi 3 chân kích mức Thấp (Active-LOW, chân IN nối đất 0V mới kêu).
// • Đặt 1: Dành cho còi kích mức Cao (Active-HIGH, chân IN mức 3.3V mới kêu).
// Ở trạng thái im lặng, hệ thống luôn đưa chân GPIO 5 về chế độ High-Z (Tri-State),
// triệt tiêu 100% dòng điện cho cả hai loại còi và chống tự kêu khi cắm nguồn.
#define BUZZER_ACTIVE_HIGH    0     // 0: Active LOW (Mặc định chuẩn module 3 chân); 1: Active HIGH
#define ENABLE_STARTUP_BEEP   0     // 0: TẮT HOÀN TOÀN âm bíp khởi động khi cắm nguồn; 1: Bật 2 tiếng bíp chào mừng
#define BUZZER_DEFAULT_MUTED  0     // 0: Còi sẵn sàng báo động; 1: Mute hoàn toàn còi khi test lab yên tĩnh
#ifdef PIN_NEOPIXEL
  #undef PIN_NEOPIXEL
#endif
#define PIN_NEOPIXEL          6     // WS2812B DIN (8 bóng RGB)
#define PIN_CANCEL_BTN        7     // OUT module touch (GPIO7, tránh GPIO0/BOOT)
#define TOUCH_ACTIVE_HIGH     1     // Module touch thường xuất HIGH khi chạm
#define NUM_LEDS              24     // Cấu hình 8 bóng LED cho thanh LED WS2812B
#define LED_BRIGHTNESS        100    // Độ sáng LED (0 - 255): 200 (~80%) sáng rõ đẹp, không bị mờ

#define PIN_I2C_SDA           8     // ToF VL53L1X SDA
#define PIN_I2C_SCL           9     // ToF VL53L1X SCL

#define PIN_RADAR_RX          18    // Nối chân TX của LD2410B
#define PIN_RADAR_TX          17    // Nối chân RX của LD2410B

// =========================================================================
// 2. THÔNG SỐ LẤY MẪU VÀ CỬA SỔ TRƯỢT
// =========================================================================
#define SAMPLE_RATE_HZ        20    // 20 Hz (50ms mỗi chu kỳ lấy mẫu)
#define WINDOW_SIZE           40    // Cửa sổ trượt 2.0 giây (40 mẫu x 50ms)
#define NUM_FEATURES          12    // 12 đặc trưng đa phương thức (ToF Multi-ROI + Radar 9 cổng + Động học)
#define ENABLE_TOF_MULTI_ROI  1     // 1: Quét 3 vùng SPAD Cao/Giữa/Thấp trên VL53L1X; 0: 1 vùng toàn khung

// =========================================================================
// 3. NGƯỠNG ĐỘ CHÍNH XÁC NHẬN DIỆN TÉ NGÃ (KINEMATIC & RADAR THRESHOLDS)
// =========================================================================
#define FALL_VELOCITY_THRESH_MM_S   550.0f  // Tốc độ sụt giảm ToF tối thiểu (>= 550 mm/s)
#define FALL_STRONG_VELOCITY_MM_S   700.0f  // Van toc cao yeu cau them bang chung san
#define FALL_RADAR_MOTION_THRESH    40      // Đỉnh năng lượng chuyển động va chạm LD2410 (>= 40/100)
#define FALL_STRONG_MOTION_THRESH   70      // Chuyen dong rat manh co the bu cho van toc ToF thap
#define POST_FALL_RADAR_MOTION_MAX  25      // Năng lượng chuyển động sau ngã (bất động <= 25/100)
#define POST_FALL_RADAR_STATIC_MIN  15      // Năng lượng tĩnh hô hấp/sự hiện diện (>= 15/100)
#define FLOOR_HEIGHT_DEFAULT_MM     450     // Chiều cao sàn: <= 450mm là tư thế nằm sàn
#define STAND_HEIGHT_MIN_MM         900     // Chiều cao đứng: >= 900mm
#define SIT_HEIGHT_MIN_MM           480     // Chiều cao ngồi: 480mm - 900mm
#define POSTURE_FLOOR_MAX_MM       450     // ToF vung than sat san: nam

#define IMMOBILE_VERIFY_TIME_MS     2000    // 2 giây theo dõi bất động sau chấn động
#define PRE_ALARM_TIMEOUT_MS        30000   // 30 giây Pre-alarm tại chỗ trước khi gửi SOS
#define RECOVERY_CONFIRM_TIME_MS    1500    // 1.5 giây đứng vững liên tục để tự giải trừ cảnh báo

// =========================================================================
// 4. CÁC TÍNH NĂNG MỞ RỘNG (SMART NIGHTLIGHT, SLOW FALL, SOS BUTTON, WATCHDOG)
// =========================================================================
#define SLOW_FALL_FLOOR_TIME_MS     15000   // 15 giây nằm sàn bất động -> Kích hoạt ngã chậm / ngất
#define MANUAL_SOS_HOLD_TIME_MS     3000    // 3 giây giữ nút BOOT -> Kích hoạt SOS thủ công khẩn cấp
#define NIGHTLIGHT_TIMEOUT_MS       40000   // 40 giây sáng đèn ngủ thông minh khi phát hiện bước chân
#define WDT_TIMEOUT_SECONDS         10      // 10 giây Hardware Watchdog chống treo hệ thống

// Cấu hình SMS Gateway & Multi-Channel Alert Bot qua Wi-Fi
#define DEFAULT_SMS_GATEWAY_URL     "https://api.speedsms.vn/index.php/sms/send"
#define DEFAULT_SMS_TOKEN           "YOUR_DEFAULT_SMS_ACCESS_TOKEN"
#define DEFAULT_ALERT_BOT_URL       "https://hearth-alert-bot.onrender.com"
#define DEFAULT_ALERT_BOT_API_KEY   ""

// Bitmask bật/tắt kênh cảnh báo từ xa (Telegram + Call, không dùng SMS)
#define CH_MASK_SMS                 0x01
#define CH_MASK_TELEGRAM            0x02
#define CH_MASK_CALL                0x04
#define CH_MASK_ALL                 (CH_MASK_TELEGRAM | CH_MASK_CALL)

// =========================================================================
// 5. ĐỊNH NGHĨA KẾT QUẢ PHÂN LOẠI VÀ TRẠNG THÁI HỆ THỐNG
// =========================================================================
enum AIClass {
  CLASS_STAND = 0,
  CLASS_SIT   = 1,
  CLASS_LIE   = 2,
  CLASS_FALL  = 3
};

enum SystemState {
  STATE_NORMAL,
  STATE_SUSPECTED,
  STATE_PRE_ALARM,
  STATE_ALERT,
  STATE_ACKNOWLEDGED,
  STATE_RESOLVED,
  STATE_DEVICE_FAULT
};

enum FallEventType {
  EVENT_NONE = 0,
  EVENT_FALL_IMPACT = 1,
  EVENT_SLOW_FALL   = 2,
  EVENT_MANUAL_SOS  = 3
};

#endif
